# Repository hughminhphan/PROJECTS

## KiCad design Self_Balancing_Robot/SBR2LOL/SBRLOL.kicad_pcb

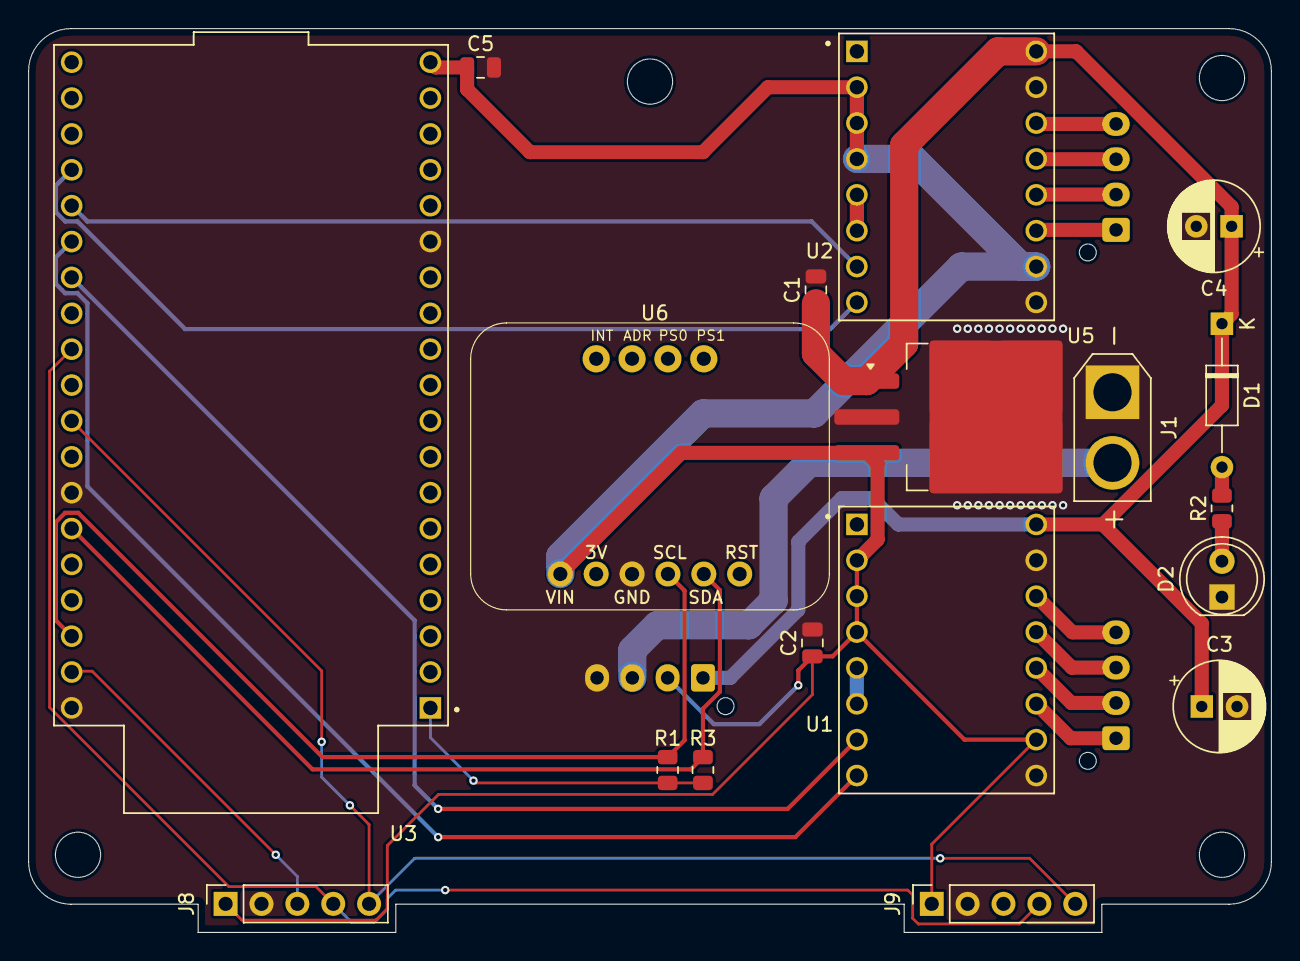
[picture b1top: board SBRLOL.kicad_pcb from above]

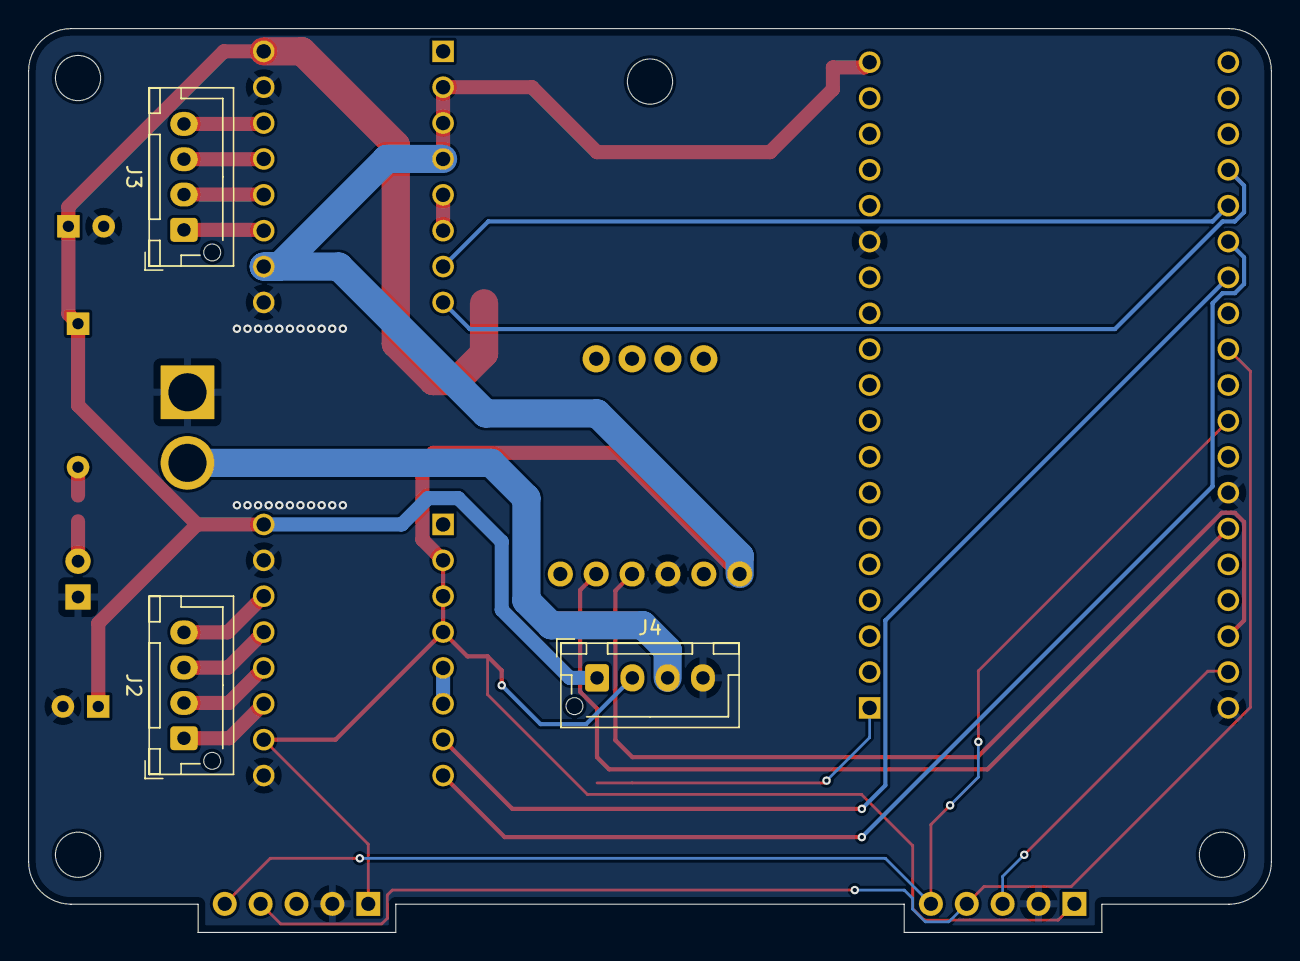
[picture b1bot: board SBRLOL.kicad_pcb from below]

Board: 2 copper layers, 88.0 x 64.0 mm, 25 parts (3 on the bottom side), 26 nets.

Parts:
C1, C2, C5: 10uF; C_0805_2012Metric
C3, C4: 100uF; CP_Radial_D6.3mm_P2.50mm
D1: 1N5243BTR; D_DO-35_SOD27_P10.16mm_Horizontal
D2: LED; LED_D5.0mm
H1, H2, H3, H4: MountingHole; MountingHole_3.2mm_M3
J1: Conn_01x02; AMASS_XT30U-M_1x02_P5.0mm_Vertical
J2, J3, J4: Conn_01x04; JST_XH_B4B-XH-AM_1x04_P2.50mm_Vertical
J8, J9: Conn_01x05; PinSocket_1x05_P2.54mm_Vertical
R1, R3: 4K7; R_0805_2012Metric
R2: 1K; R_0805_2012Metric
U1, U2: A4988_STEPPER_MOTOR_DRIVER_CARRIER; MODULE_A4988_STEPPER_MOTOR_DRIVER_CARRIER
U3: ESP32-DEVKITC; MODULE_ESP32-DEVKITC
U5: uA7805; TO-263-3_TabPin2
U6: Adafruit IMU BNO055

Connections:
+3V3: R1.2, R3.2, U3.1 (3V3)
+5V: C2.1, C5.1, J4.2, J8.1, J9.1, U1.2 (MS1), U1.3 (MS2), U1.4 (MS3), U1.10 (VDD), U2.2 (MS1), U2.3 (MS2), U2.4 (MS3), U2.10 (VDD), U3.19 (EXT_5V), U5.3 (OUT), U6.1 (VIN)
+15V: C1.1, C3.1, C4.1, D1.1 (K), J4.1, U1.16 (VMOT), U2.16 (VMOT), U5.1 (IN)
/CLK: J8.5, J9.5, U3.30 (IO18)
/CS1: J8.4, J9.4, U3.28 (IO17)
/DIN: J8.3, U3.37 (IO23)
/M1DIR: U1.8 (DIR), U3.25 (IO0)
/M1STEP: U1.7 (STEP), U3.26 (IO4)
/M2DIR: U2.8 (DIR), U3.23 (IO15)
/M2STEP: U2.7 (STEP), U3.24 (IO2)
/SCL: R1.1, U3.36 (IO22), U6.4 (SCL)
/SDA: R3.1, U3.33 (IO21), U6.5 (SDA)
GND: C1.2, C2.2, C3.2, C4.2, C5.2, D2.1 (K), J1.1, J4.4, J8.2, J9.2, U1.9 (GND), U1.15 (GND__1), U2.9 (GND), U2.15 (GND__1), U3.14 (GND1), U3.32 (GND2), U3.38 (GND3), U5.2 (GND), U6.3 (GND)
unnamed: D1.2 (A), R2.2
unnamed: D2.2 (A), R2.1
unnamed: J1.2, J4.3
unnamed: J2.1, U1.11 (1B)
unnamed: J2.2, U1.12 (1A)
unnamed: J2.3, U1.13 (2A)
unnamed: J2.4, U1.14 (2B)
unnamed: J3.1, U2.11 (1B)
unnamed: J3.2, U2.12 (1A)
unnamed: J3.3, U2.13 (2A)
unnamed: J3.4, U2.14 (2B)
unnamed: U1.5 (~RESET), U1.6 (~SLEEP)
unnamed: U2.5 (~RESET), U2.6 (~SLEEP)

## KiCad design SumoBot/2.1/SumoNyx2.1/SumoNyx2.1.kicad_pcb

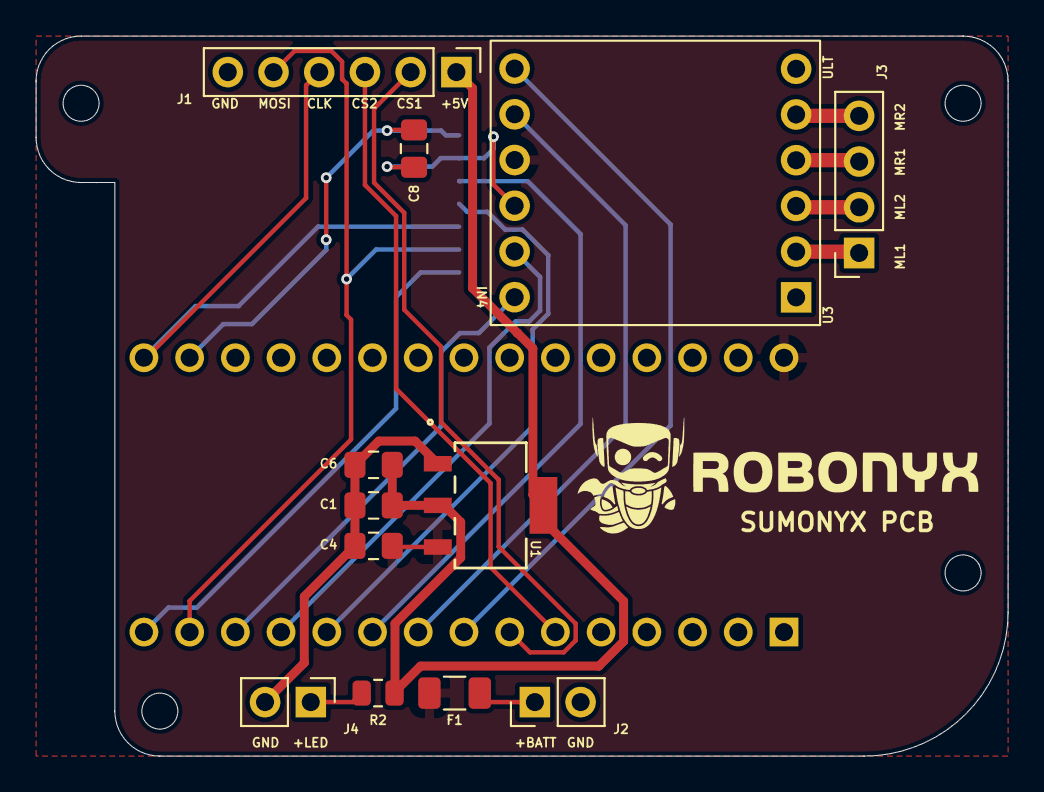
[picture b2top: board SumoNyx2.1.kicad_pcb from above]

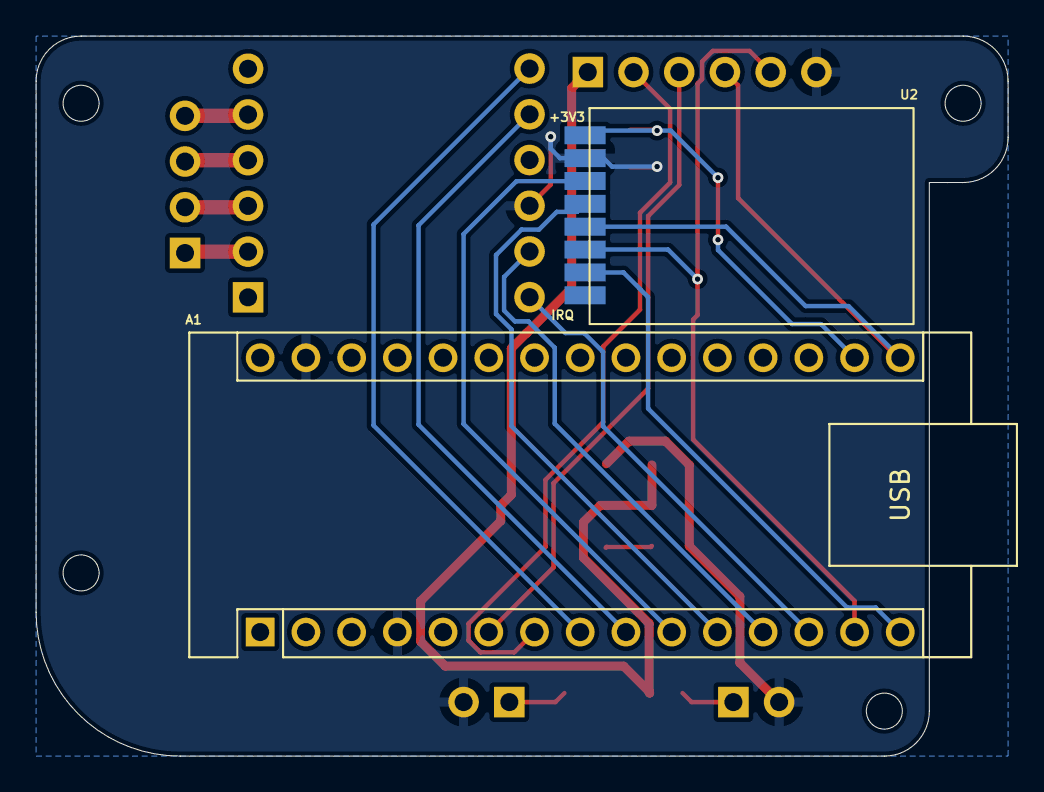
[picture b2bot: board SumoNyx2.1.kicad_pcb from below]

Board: 2 copper layers, 54.0 x 40.0 mm, 14 parts (2 on the bottom side), 21 nets.

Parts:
A1: Arduino_Nano_v3.x; Arduino_Nano
C1, C6: 22UF10V; C_0805_2012Metric_Pad1.18x1.45mm_HandSolder
C4, C8: 10UF10V; C_0805_2012Metric_Pad1.18x1.45mm_HandSolder
F1: SMD1206B110TFT_Polyfuse; Fuse_1206_3216Metric
J1: Conn_01x06_Male; PinHeader_1x06_P2.54mm_Vertical
J2: BATT 7V5; PinHeader_1x02_P2.54mm_Vertical
J3: MOTOR; PinSocket_1x04_P2.54mm_Vertical
J4: BACK 7 LED; PinHeader_1x02_P2.54mm_Vertical
R2: 50R; R_0805_2012Metric
U1: AZ1117IH-5.0TRG1; SOT223-5_DIO
U2: NRF24L01_Breakout; nRF24L01_Breakout_SMD
U3: DRV8833BRKT

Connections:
+3.3V: A1.17 (3V3), C8.2, U2.2 (VCC)
+5V: C1.2, C6.2, J1.1, R2.1, U1.2 (OUTPUT), U1.4 (VOUT)
+7.5V: A1.30 (VIN), C4.2, F1.2, U1.3 (INPUT), U3.10 (VM)
/MOTA1: J3.1, U3.2 (AOUT1)
/MOTA2: J3.2, U3.3 (AOUT2)
/MOTB1: J3.3, U3.4 (BOUT1)
/MOTB2: J3.4, U3.5 (BOUT2)
GND: A1.4 (GND), A1.29 (GND), C1.1, C4.1, C6.1, C8.1, J1.6, J2.2, J4.2, U1.1 (ADJ/GND), U2.1 (GND), U3.9 (GND)
unnamed: A1.6 (D3), J1.3
unnamed: A1.7 (D4), J1.2
unnamed: A1.8 (D5), U3.12 (AIN1)
unnamed: A1.9 (D6), U3.11 (AIN2)
unnamed: A1.10 (D7), U2.3 (CE)
unnamed: A1.11 (D8), U2.4 (~CSN)
unnamed: A1.12 (D9), U3.8 (BIN1)
unnamed: A1.13 (D10), U3.7 (BIN2)
unnamed: A1.14 (D11), J1.5, U2.6 (MOSI)
unnamed: A1.15 (D12), U2.7 (MISO)
unnamed: A1.16 (D13), J1.4, U2.5 (SCK)
unnamed: F1.1, J2.1
unnamed: J4.1, R2.2

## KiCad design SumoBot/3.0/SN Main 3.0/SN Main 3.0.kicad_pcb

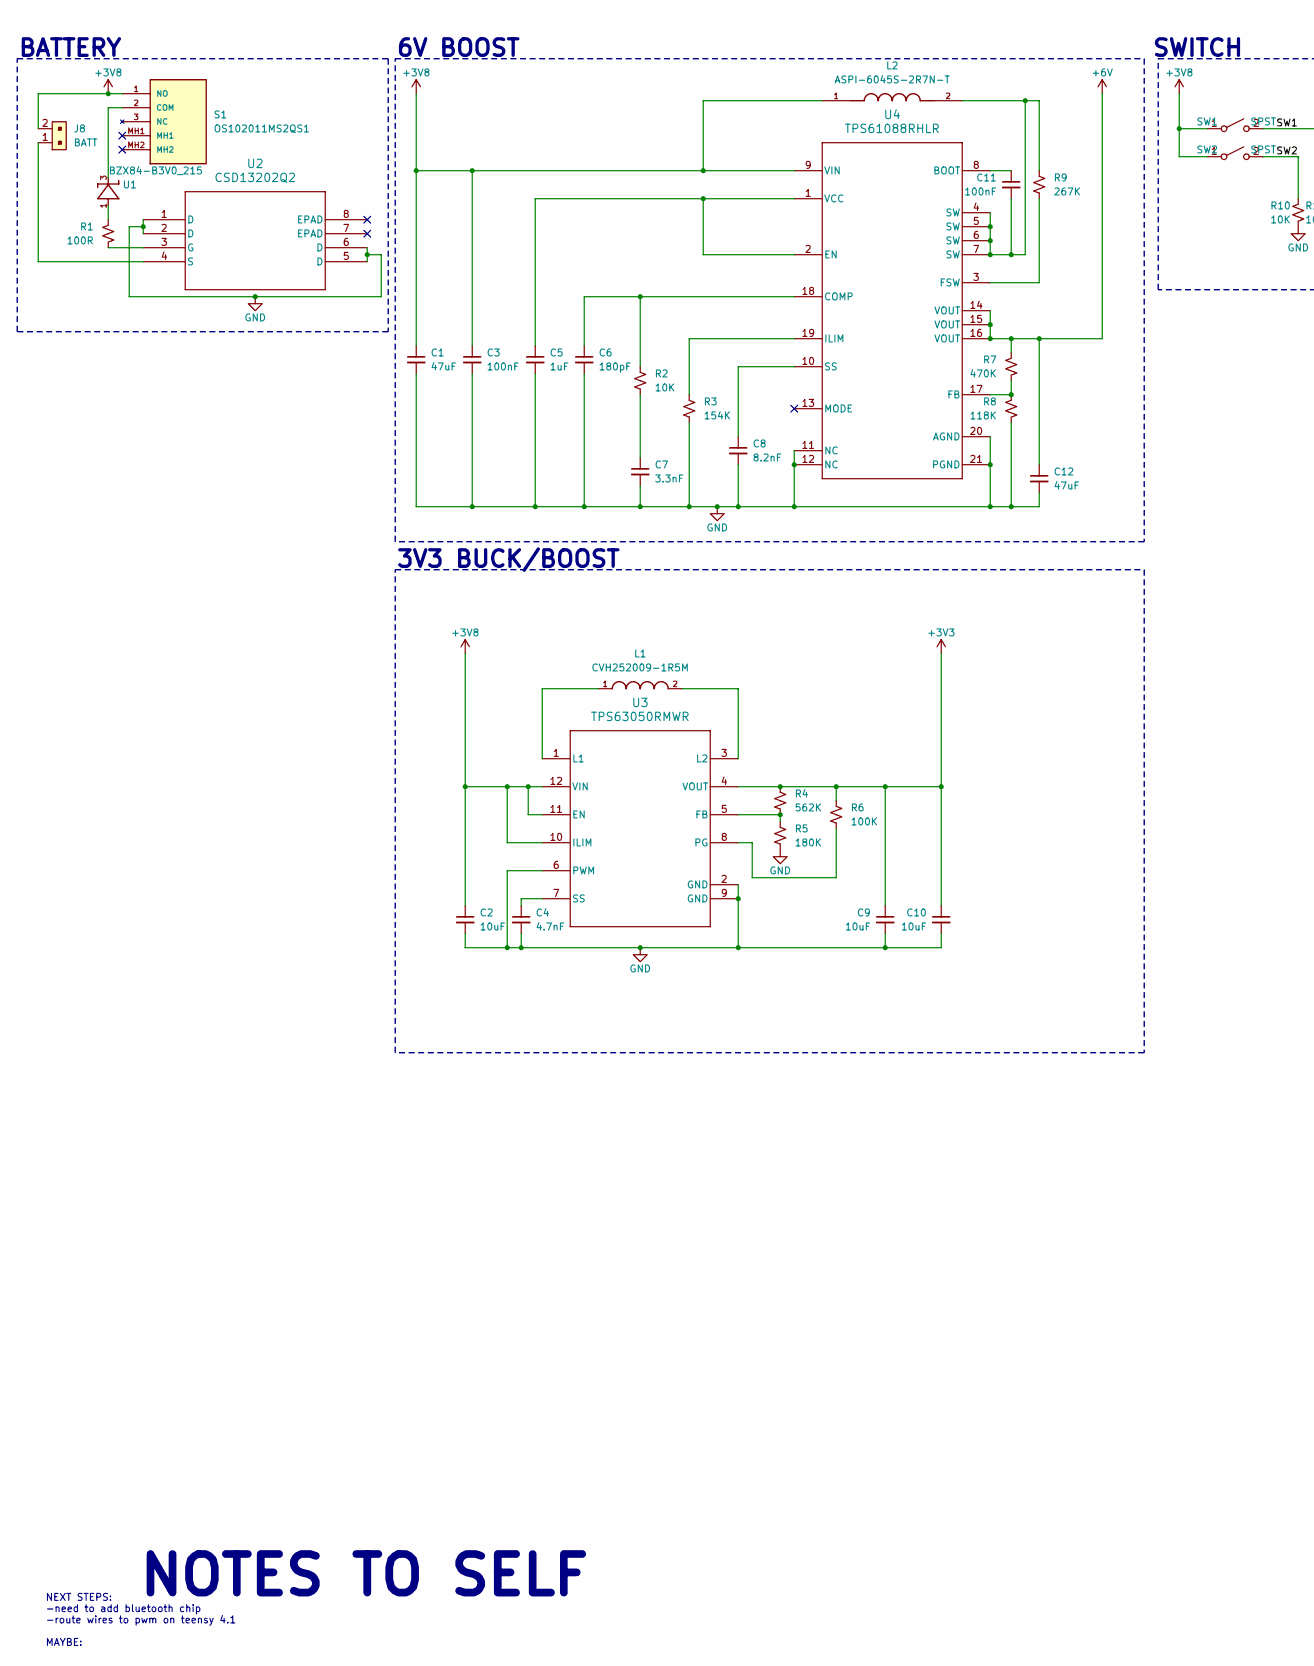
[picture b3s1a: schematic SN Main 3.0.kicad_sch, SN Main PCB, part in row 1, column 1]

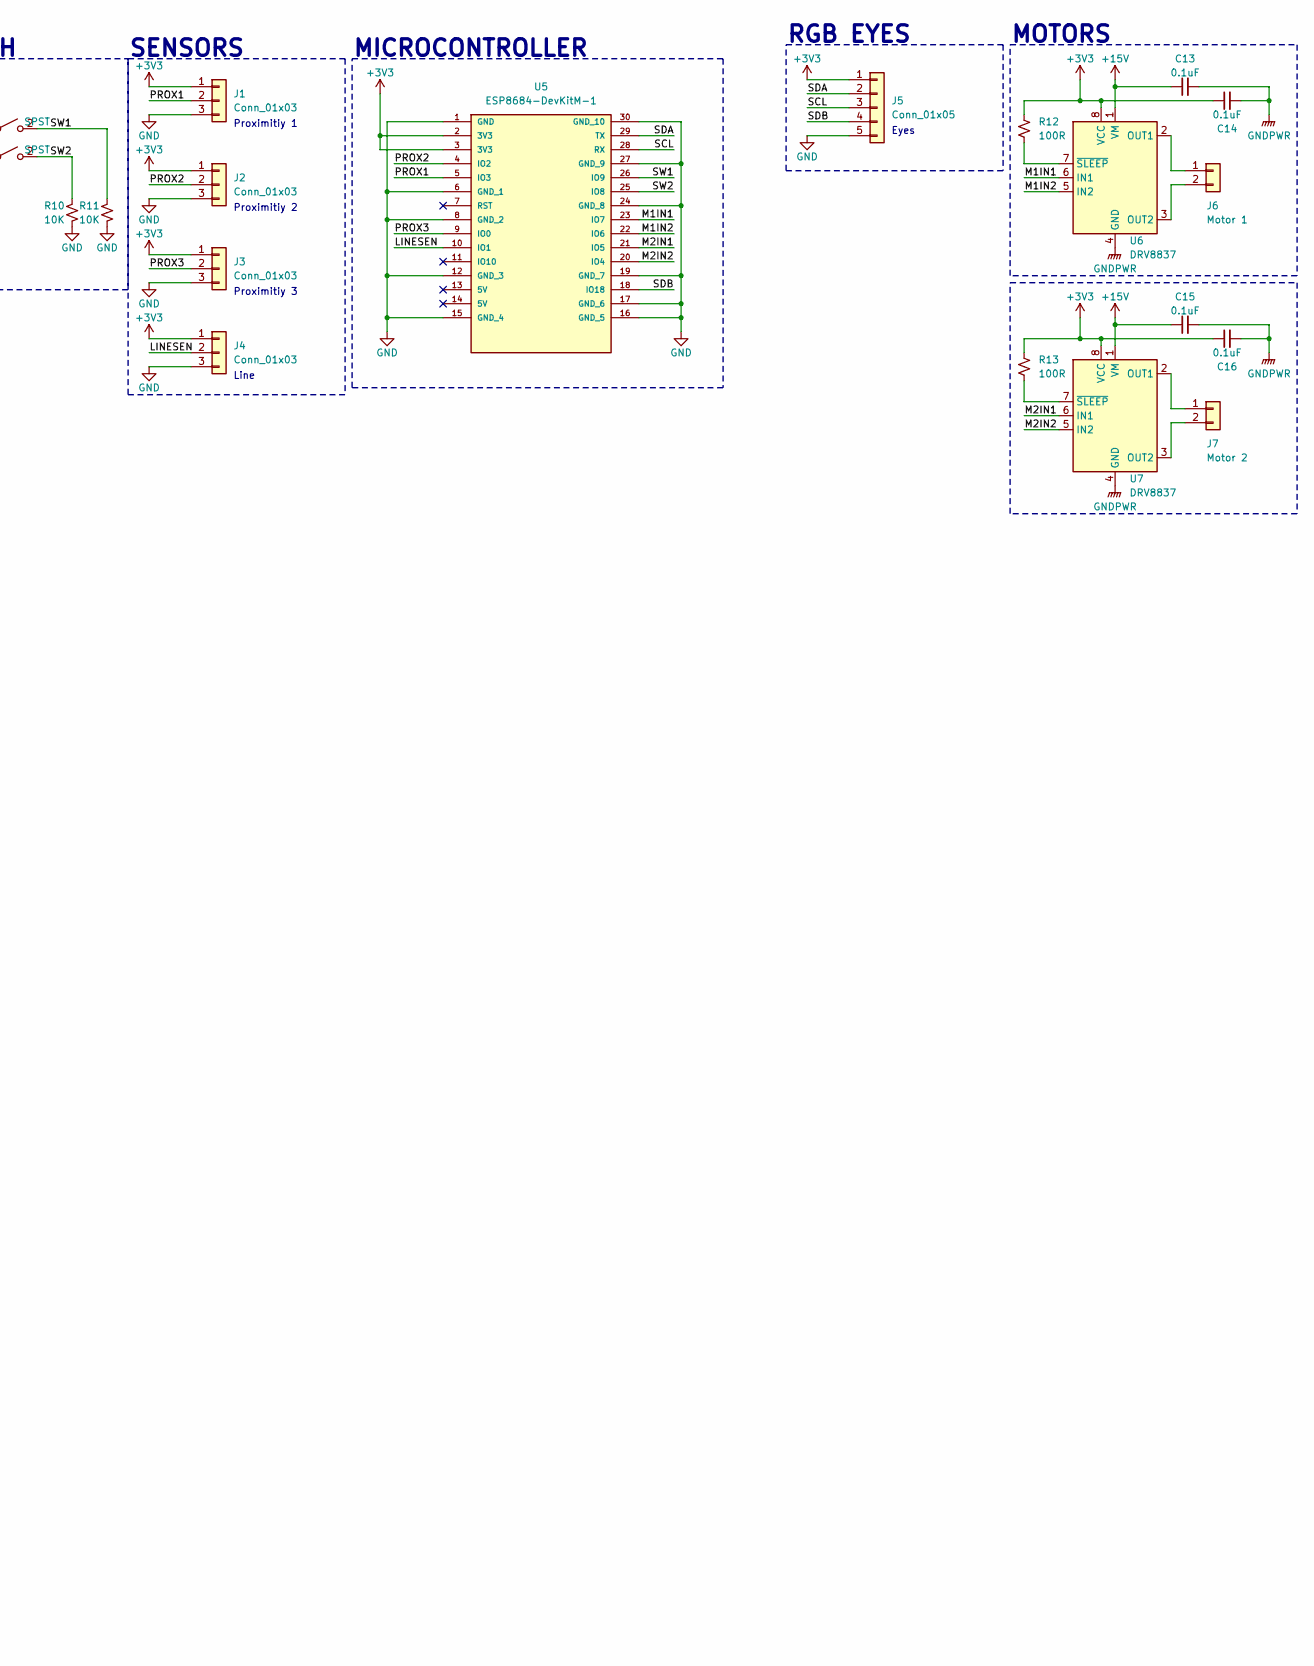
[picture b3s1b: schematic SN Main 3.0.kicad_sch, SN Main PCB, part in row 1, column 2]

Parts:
C1, C12: 47uF; C_0805_2012Metric
C2, C9, C10: 10uF; C_0805_2012Metric
C3, C11: 100nF; C_0805_2012Metric
C4: 4.7nF; C_0805_2012Metric
C5: 1uF; C_0805_2012Metric
C6: 180pF; C_0805_2012Metric
C7: 3.3nF; C_0805_2012Metric
C8: 8.2nF; C_0805_2012Metric
C13, C14, C15, C16: 0.1uF; C_0805_2012Metric
J1, J2, J3, J4: Conn_01x03; JST_XH_B3B-XH-A_1x03_P2.50mm_Vertical
J5: Conn_01x05; JST_XH_B5B-XH-A_1x05_P2.50mm_Vertical
J6: Motor 1; AMASS_XT30U-F_1x02_P5.0mm_Vertical
J7: Motor 2; AMASS_XT30U-F_1x02_P5.0mm_Vertical
J8: BATT; PinHeader_1x2_P2.5mm_Drill1.1mm; MPN B2B-XH-A(LF)(SN); Digi-Key_PN 455-2247-ND
L1: CVH252009-1R5M; INDC2520X100N
L2: ASPI-6045S-2R7N-T; IND_ASPI-6045S-2R7N-T; PARTREV 2/22/2016
R1, R12, R13: 100R; R_0805_2012Metric
R2, R10, R11: 10K; R_0805_2012Metric
R3: 154K; R_0805_2012Metric
R4: 562K; R_0805_2012Metric
R5: 180K; R_0805_2012Metric
R6: 100K; R_0805_2012Metric
R7: 470K; R_0805_2012Metric
R8: 118K; R_0805_2012Metric
R9: 267K; R_0805_2012Metric
S1: OS102011MS2QS1; MOUSER_PART_NUMBER 611-OS102011MS2QS1
SW1, SW2: SPST; SW_PUSH_6mm_H4.3mm
U1: BZX84-B3V0_215; SOT23
U2: CSD13202Q2; DQK6_TEX
U3: TPS63050RMWR; RMW0012A
U4: TPS61088RHLR; RHL0020A
U5: ESP8684-DevKitM-1
U6, U7: DRV8837; WSON-8-1EP_2x2mm_P0.5mm_EP0.9x1.6mm

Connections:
+3V3: C9.1, C10.1, C14.1, C16.1, J1.1, J2.1, J3.1, J4.1, J5.1, R4.1, R6.1, R12.1, R13.1, U3.4 (VOUT), U5.2 (3V3), U5.3 (3V3), U6.8 (VCC), U7.8 (VCC)
+3V8: C1.1, C2.1, C3.1, J8.2, L2.1, S1.1 (NO), SW1.1 (A), SW2.1 (A), U3.10 (ILIM), U3.11 (EN), U3.12 (VIN), U4.9 (VIN)
+6V: C12.1, R7.1, U4.14 (VOUT), U4.15 (VOUT), U4.16 (VOUT)
+15V: C13.1, C15.1, U6.1 (VM), U7.1 (VM)
/LINESEN: J4.2, U5.10 (IO1)
/M1IN1: U5.23 (IO7), U6.6 (IN1)
/M1IN2: U5.22 (IO6), U6.5 (IN2)
/M2IN1: U5.21 (IO5), U7.6 (IN1)
/M2IN2: U5.20 (IO4), U7.5 (IN2)
/PROX1: J1.2, U5.5 (IO3)
/PROX2: J2.2, U5.4 (IO2)
/PROX3: J3.2, U5.9 (IO0)
/SCL: J5.3, U5.28 (RX)
/SDA: J5.2, U5.29 (TX)
/SDB: J5.4, U5.18 (IO18)
/SW1: R11.1, SW1.2 (B), U5.26 (IO9)
/SW2: R10.1, SW2.2 (B), U5.25 (IO8)
GND: C1.2, C2.2, C3.2, C4.2, C5.2, C6.2, C7.2, C8.2, C9.2, C10.2, C12.2, J1.3, J2.3, J3.3, J4.3, J5.5, R3.2, R5.2, R8.2, R10.2, R11.2, U2.1 (D), U2.2 (D), U2.5 (D), U2.6 (D), U3.2 (GND), U3.6 (PWM), U3.9 (GND), U4.11 (NC), U4.12 (NC), U4.20 (AGND), U4.21 (PGND), U5.1 (GND), U5.6 (GND_1), U5.8 (GND_2), U5.12 (GND_3), U5.15 (GND_4), U5.16 (GND_5), U5.17 (GND_6), U5.19 (GND_7), U5.24 (GND_8), U5.27 (GND_9), U5.30 (GND_10)
GNDPWR: C13.2, C14.2, C15.2, C16.2, U6.4 (GND), U6.9 (GND), U7.4 (GND), U7.9 (GND)
unnamed: C7.1, R2.2
unnamed: C11.2, L2.2, R9.1, U4.4 (SW), U4.5 (SW), U4.6 (SW), U4.7 (SW)
unnamed: J6.1, U6.2 (OUT1)
unnamed: J6.2, U6.3 (OUT2)
unnamed: J7.1, U7.2 (OUT1)
unnamed: J7.2, U7.3 (OUT2)
unnamed: R1.1, U1.1
unnamed: S1.2 (COM), U1.3
unnamed: R1.2, U2.3 (G)
unnamed: J8.1, U2.4 (S)
unnamed: R4.2, R5.1, U3.5 (FB)
unnamed: L1.1, U3.1 (L1)
unnamed: L1.2, U3.3 (L2)
unnamed: R6.2, U3.8 (PG)
unnamed: C4.1, U3.7 (SS)
unnamed: C11.1, U4.8 (BOOT)
unnamed: C6.1, R2.1, U4.18 (COMP)
unnamed: C5.1, U4.1 (VCC), U4.2 (EN)
unnamed: R7.2, R8.1, U4.17 (FB)
unnamed: R9.2, U4.3 (FSW)
unnamed: R3.1, U4.19 (ILIM)
unnamed: C8.1, U4.10 (SS)
unnamed: R12.2, U6.7 (~SLEEP)
unnamed: R13.2, U7.7 (~SLEEP)

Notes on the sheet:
SWITCH
NOTES TO SELF
6V BOOST
NEXT STEPS: -need to add bluetooth chip -route wires to pwm on teensy 4.1 MAYBE:
Eyes
Proximitiy 3
Proximitiy 1
MOTORS
SENSORS
Proximitiy 2
Line
RGB EYES
BATTERY
3V3 BUCK/BOOST
MICROCONTROLLER

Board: 2 copper layers, 49 parts (0 on the bottom side), 43 nets, no tracks yet.

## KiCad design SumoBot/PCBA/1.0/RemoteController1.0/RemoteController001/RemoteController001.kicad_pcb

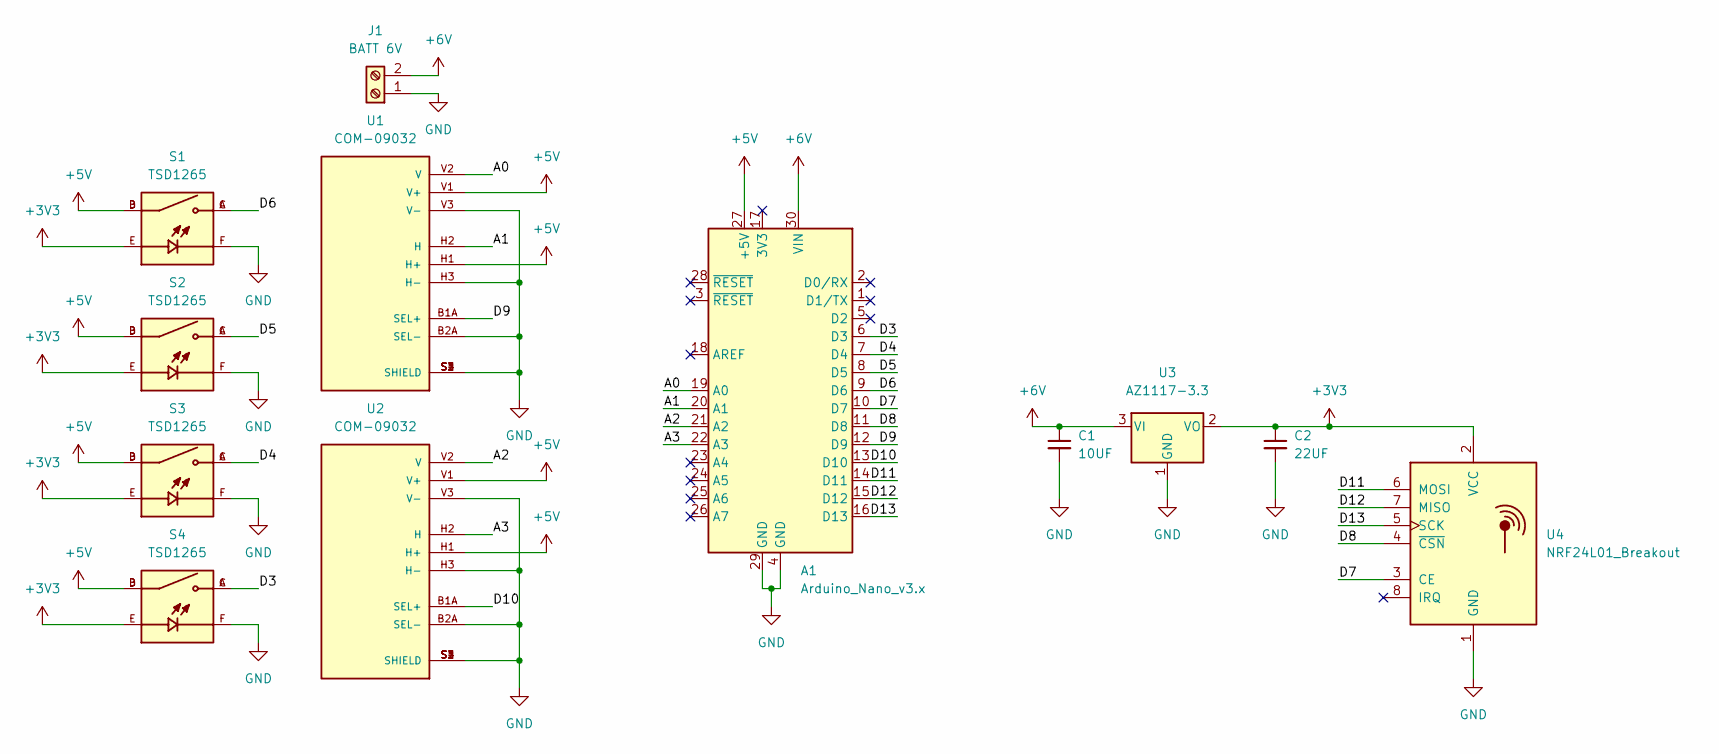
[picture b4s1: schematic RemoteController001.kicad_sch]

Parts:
A1: Arduino_Nano_v3.x; Arduino_Nano
C1: 10UF; C_0805_2012Metric_Pad1.18x1.45mm_HandSolder
C2: 22UF; C_0805_2012Metric_Pad1.18x1.45mm_HandSolder
J1: BATT 6V
S1, S2, S3, S4: TSD1265; SW_TSD1265; PARTREV N/A
U1, U2: COM-09032; XDCR_COM-09032; PARTREV N/A
U3: AZ1117-3.3; SOT-89-3_Handsoldering
U4: NRF24L01_Breakout; nRF24L01_Breakout

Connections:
+3V3: C2.1, S1.E, S2.E, S3.E, S4.E, U3.2 (VO), U4.2 (VCC)
+5V: A1.27 (+5V), S1.B, S1.D, S2.B, S2.D, S3.B, S3.D, S4.B, S4.D, U1.H1 (H+), U1.V1 (V+), U2.H1 (H+), U2.V1 (V+)
+6V: A1.30 (VIN), C1.1, J1.2, U3.3 (VI)
/A0: A1.19 (A0), U1.V2 (V)
/A1: A1.20 (A1), U1.H2 (H)
/A2: A1.21 (A2), U2.V2 (V)
/A3: A1.22 (A3), U2.H2 (H)
/D3: A1.6 (D3), S4.A, S4.C
/D4: A1.7 (D4), S3.A, S3.C
/D5: A1.8 (D5), S2.A, S2.C
/D6: A1.9 (D6), S1.A, S1.C
/D7: A1.10 (D7), U4.3 (CE)
/D8: A1.11 (D8), U4.4 (~CSN)
/D9: A1.12 (D9), U1.B1A (SEL+)
/D10: A1.13 (D10), U2.B1A (SEL+)
/D11: A1.14 (D11), U4.6 (MOSI)
/D12: A1.15 (D12), U4.7 (MISO)
/D13: A1.16 (D13), U4.5 (SCK)
GND: A1.4 (GND), A1.29 (GND), C1.2, C2.2, J1.1, S1.F, S2.F, S3.F, S4.F, U1.B2A (SEL-), U1.H3 (H-), U1.S1 (SHIELD), U1.S2 (SHIELD), U1.S3 (SHIELD), U1.S4 (SHIELD), U1.V3 (V-), U2.B2A (SEL-), U2.H3 (H-), U2.S1 (SHIELD), U2.S2 (SHIELD), U2.S3 (SHIELD), U2.S4 (SHIELD), U2.V3 (V-), U3.1 (GND), U4.1 (GND)

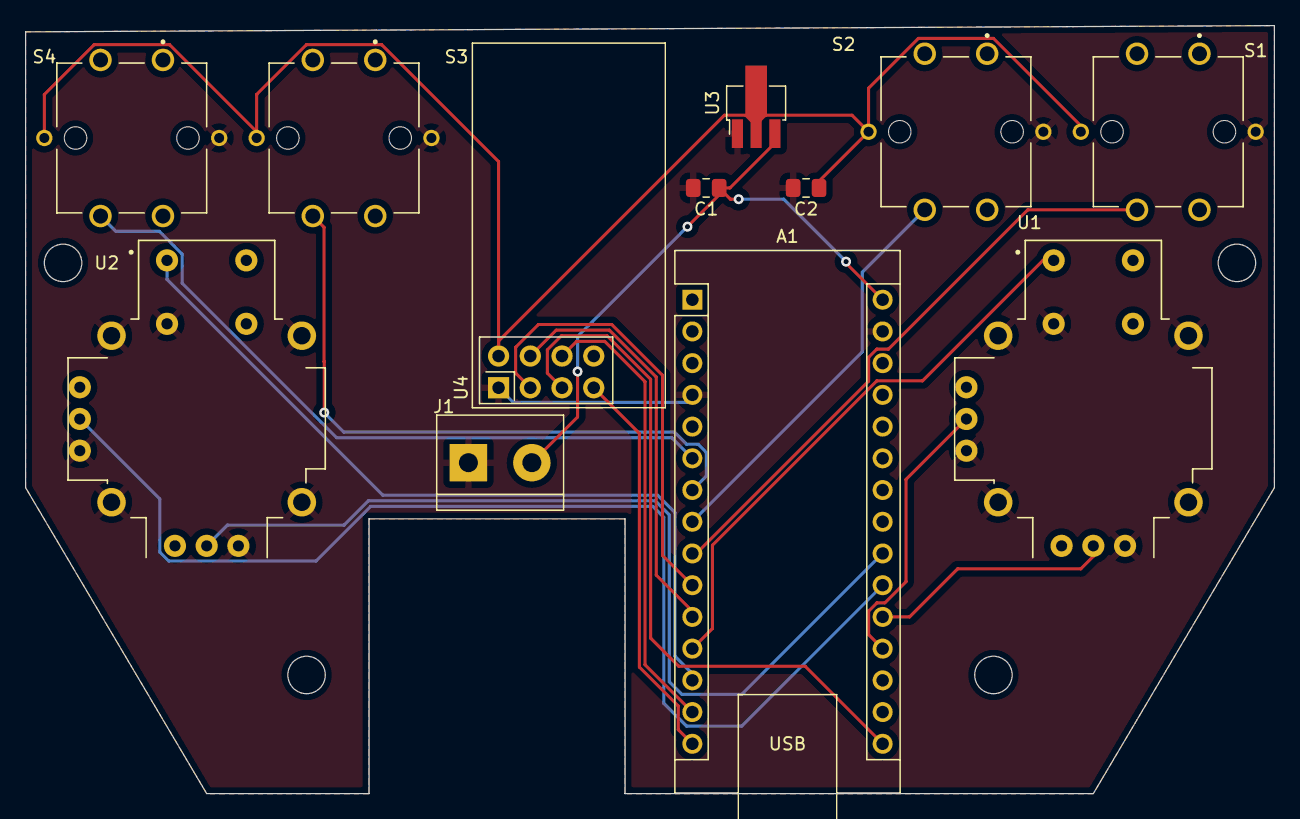
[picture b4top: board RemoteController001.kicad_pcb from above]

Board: 2 copper layers, 100.0 x 61.5 mm, 12 parts (0 on the bottom side), 19 nets.
